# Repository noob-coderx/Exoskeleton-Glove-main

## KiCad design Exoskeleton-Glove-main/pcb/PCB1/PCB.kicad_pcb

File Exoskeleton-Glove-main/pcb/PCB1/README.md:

In a nutshell, our design collects data from rotary potentiometers serially, sends them to Rpi pico which in turn quickly cycles through the available channels in a round robin fashion while powering everything using an LM2596 Buck converter

Our PCB design has the ability to support upto 24 rotary potentiometers due to which we have 24 ports connected to ground and 24 ports connected to VCC(3.3V output from sensor). We connected these to the 3.3v supply of Pico instead of our main power supply which is LM2596 because cd74hc4067 multiplexers are designed to take an input between 0 and 3.3V.
External power is inputted at the 2x1 connector which is also the input of out LM2596 buck converter, the output of this converter powers both our cd74hc multiplexers. Raspberry pico runs a program in which it outputs different values periodically at 4 different GPIO pins(2,3,4,5) which are connected to s0,s1,s2,s3 of multiplexer 1 and GPIO pins(18,19,20,21) which are connected to s0,s1,s2,s3 of multiplexer 2. The output of each of the multiplexers(sig) is connected to 2 out of 3 ADC pins in rpi pico(GPIO 26,27,28). This output is transmitted to unity and esp32 which controls the prosthetic arm

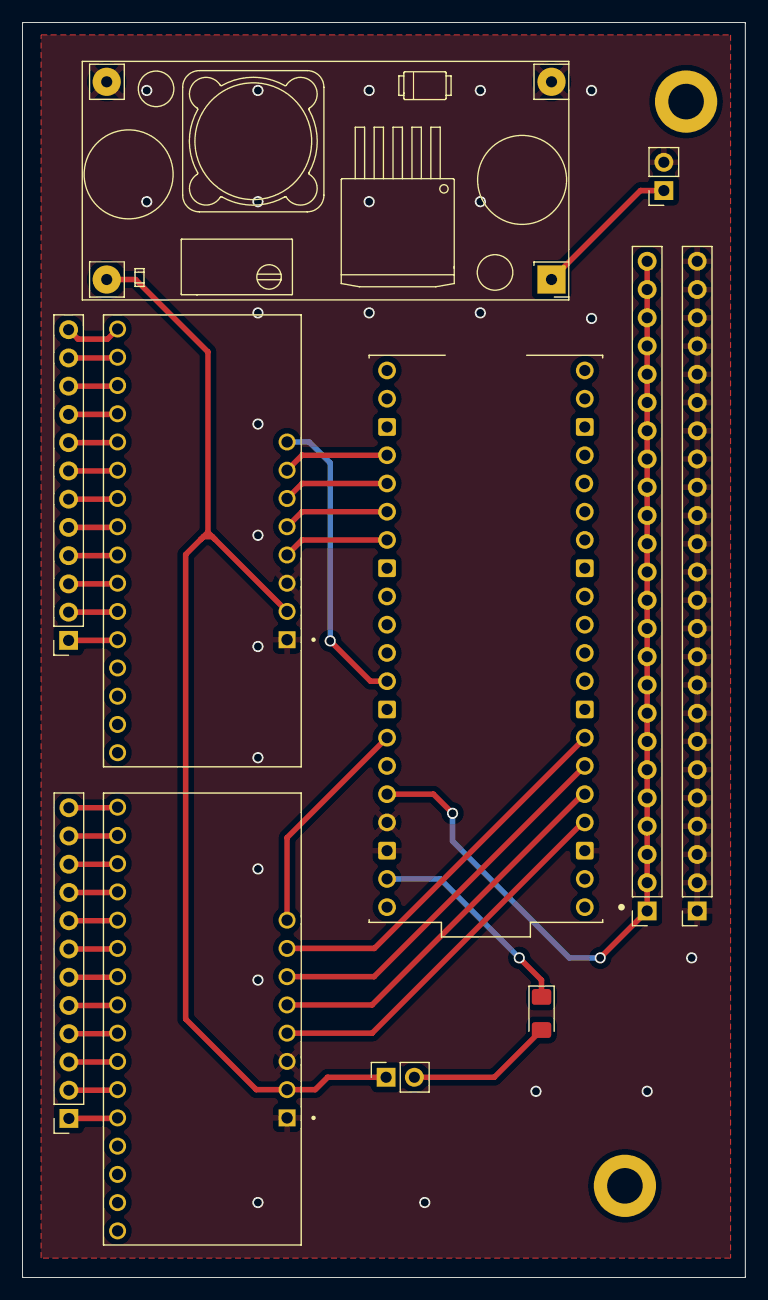
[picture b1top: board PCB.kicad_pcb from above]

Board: 2 copper layers, 65.0 x 112.8 mm, 13 parts (0 on the bottom side), 40 nets.

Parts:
A1: SC0918; MODULE_SC0918
D1: D_Schottky; D_1206_3216Metric_Pad1.42x1.75mm_HandSolder
H1, H2: MountingHole_Pad; MountingHole_3.2mm_M3_DIN965_Pad
J1, J2: Conn_01x12_Pin; PinSocket_1x12_P2.54mm_Vertical
J3, J6: Conn_01x02_Pin; PinSocket_1x02_P2.54mm_Vertical
J4, J5: Conn_01x24_Socket; PinSocket_1x24_P2.54mm_Vertical
U1, U2: BOB-09056; MODULE_BOB-09056
U6: YAAJ_DCDC_StepDown_LM2596

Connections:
/Out_1: A1.34 (GP28), U1.JP3-8 (COM)
/Out_2: A1.32 (GP27), U2.JP3-8 (COM)
/S0: A1.24 (GP18), U2.JP3-7 (S3)
/S0_2: A1.7 (GP5), U1.JP3-7 (S3)
/S1: A1.25 (GP19), U2.JP3-6 (S2)
/S1_2: A1.6 (GP4), U1.JP3-6 (S2)
/S2: A1.26 (GP20), U2.JP3-5 (S1)
/S2_2: A1.5 (GP3), U1.JP3-5 (S1)
/S3: A1.27 (GP21), U2.JP3-4 (S0)
/S3_2: A1.4 (GP2), U1.JP3-4 (S0)
GND: A1.3 (GND), A1.37 (3V3_EN), A1.38 (GND), J3.2, J4.1, J4.2, J4.3, J4.4, J4.5, J4.6, J4.7, J4.8, J4.9, J4.10, J4.11, J4.12, J4.13, J4.14, J4.15, J4.16, J4.17, J4.18, J4.19, J4.20, J4.21, J4.22, J4.23, J4.24, U1.JP3-1 (GND), U1.JP3-3 (EN), U2.JP3-1 (GND), U2.JP3-3 (EN), U6.2 (GND), U6.3 (GND)
unnamed: A1.36 (3V3_OUT), J5.1, J5.2, J5.3, J5.4, J5.5, J5.6, J5.7, J5.8, J5.9, J5.10, J5.11, J5.12, J5.13, J5.14, J5.15, J5.16, J5.17, J5.18, J5.19, J5.20, J5.21, J5.22, J5.23, J5.24
unnamed: A1.39 (VSYS), D1.1 (K)
unnamed: D1.2 (A), J6.2
unnamed: J1.1, U1.JP1-5 (C4)
unnamed: J1.2, U1.JP1-6 (C5)
unnamed: J1.3, U1.JP1-7 (C6)
unnamed: J1.4, U1.JP1-8 (C7)
unnamed: J1.5, U1.JP1-9 (C8)
unnamed: J1.6, U1.JP1-10 (C9)
unnamed: J1.7, U1.JP1-11 (C10)
unnamed: J1.8, U1.JP1-12 (C11)
unnamed: J1.9, U1.JP1-13 (C12)
unnamed: J1.10, U1.JP1-14 (C13)
unnamed: J1.11, U1.JP1-15 (C14)
unnamed: J1.12, U1.JP1-16 (C15)
unnamed: J2.1, U2.JP1-5 (C4)
unnamed: J2.2, U2.JP1-6 (C5)
unnamed: J2.3, U2.JP1-7 (C6)
unnamed: J2.4, U2.JP1-8 (C7)
unnamed: J2.5, U2.JP1-9 (C8)
unnamed: J2.6, U2.JP1-10 (C9)
unnamed: J2.7, U2.JP1-11 (C10)
unnamed: J2.8, U2.JP1-12 (C11)
unnamed: J2.9, U2.JP1-13 (C12)
unnamed: J2.10, U2.JP1-14 (C13)
unnamed: J2.11, U2.JP1-15 (C14)
unnamed: J2.12, U2.JP1-16 (C15)
unnamed: J3.1, U6.1 (Vin)
unnamed: J6.1, U1.JP3-2 (VCC), U2.JP3-2 (VCC), U6.4 (Vout)

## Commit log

2025-09-30 edit
